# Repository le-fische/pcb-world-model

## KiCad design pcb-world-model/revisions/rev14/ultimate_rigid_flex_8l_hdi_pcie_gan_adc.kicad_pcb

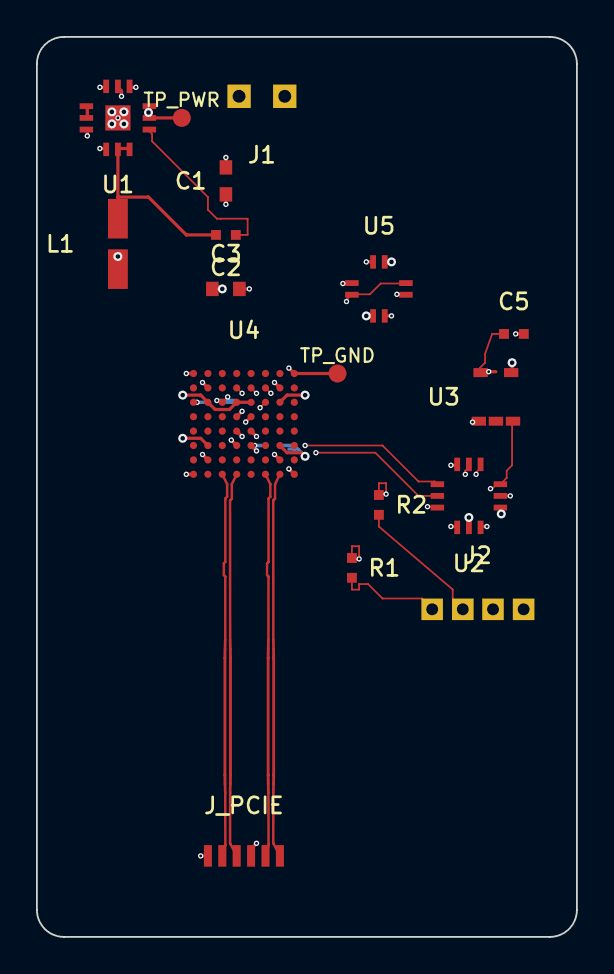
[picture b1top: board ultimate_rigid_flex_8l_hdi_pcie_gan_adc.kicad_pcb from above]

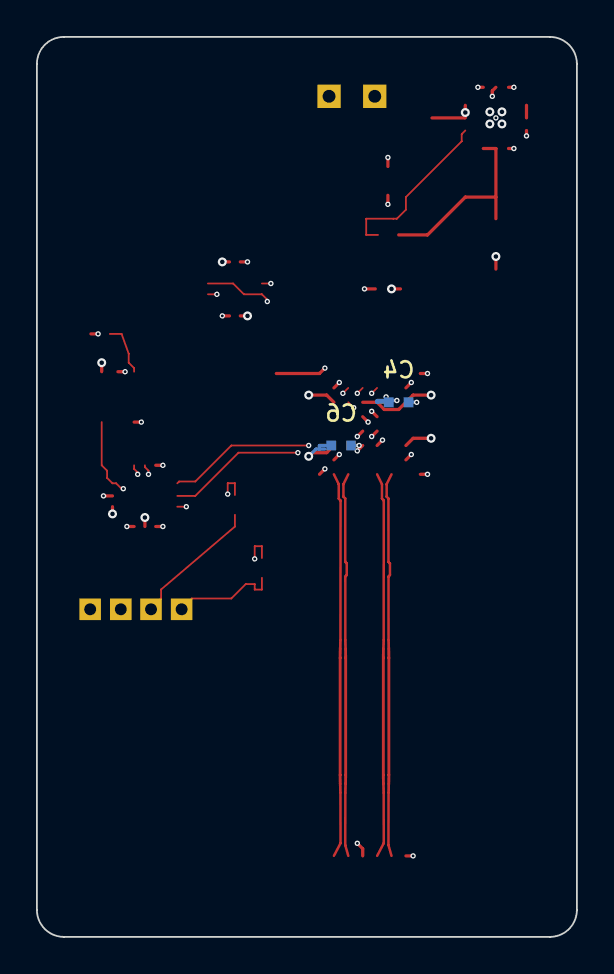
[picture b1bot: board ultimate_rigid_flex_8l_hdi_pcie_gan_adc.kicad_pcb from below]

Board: 8 copper layers, 30.0 x 50.0 mm, 19 parts (2 on the bottom side), 19 nets.

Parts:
C1: 10uF_VIN; C_0603_1608Metric
C2: 100nF_BOOT; C_0402_1005Metric
C3: 22uF_3V3; C_0603_1608Metric
C4: 100nF_PDN1; C_0402_1005Metric
C5: 100nF_VREF; C_0402_1005Metric
C6: 100nF_PDN2; C_0402_1005Metric
J1: PWR_12V_IN; PinHeader_1x02_P2.54mm_Horizontal
J2: SUBMV_ANALOG_IN; PinHeader_1x04_P1.70mm_Horizontal
J_PCIE: PCIE_GEN4_B2B; DF40C-6DP-0.8V
L1: 2.2uH_GAN_SW; L_3.5x3.5_H1.8
R1: 100R_AINP; R_0402_1005Metric
R2: 100R_AINN; R_0402_1005Metric
TP_GND: TestPoint_Pad_D1.0mm
TP_PWR: TestPoint_Pad_D1.0mm
U1: LMG5200_GAN_5A_2MHZ; QFN-12_3.5x3.5mm_P0.65mm
U2: ADS1256_24B_ADC; QFN-12_3.5x3.5mm_P0.65mm
U3: REF5025_VREF; SOT-23-5
U4: ECP5_FPGA_BGA64; BGA-64_7.2x7.2mm_Layout8x8_P0.8mm
U5: W25Q16_QSPI; QFN-8_3.0x3.0mm_P0.65mm

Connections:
ADC_AINN: R2.2, U2.5
ADC_AINP: R1.2, U2.4
ADC_CS_N: U2.9, U4.B6
BOOT_SW: C2.1, U1.7
GND: C1.2, C3.2, C4.2, C5.2, C6.2, J1.2, J2.4, J_PCIE.1, J_PCIE.4, TP_GND.1, U1.3, U1.4, U1.10, U1.12, U1.13, U2.2, U2.6, U2.10, U2.12, U3.2, U3.4, U4.A1, U4.A8, U4.B2, U4.B7, U4.D4, U4.D5, U4.E4, U4.E5, U4.F4, U4.F5, U4.G2, U4.G7, U4.H1, U4.H8, U5.4, U5.8
PCIE_CLK_N: J_PCIE.6, U4.H7
PCIE_CLK_P: J_PCIE.5, U4.H6
PCIE_TX0_N: J_PCIE.3, U4.H4
PCIE_TX0_P: J_PCIE.2, U4.H3
QSPI_CS: U4.C6, U5.2, U5.6
QSPI_SCK: U4.C3, U5.1, U5.5
SENS_N_IN: J2.2, R2.1
SENS_P_IN: J2.1, R1.1
SPI_MISO: U2.8, U4.B5
SPI_SCK: U2.7, U4.B4
SW_NODE: C2.2, L1.1, U1.5, U1.6
VCC_3V3: C3.1, C4.1, C6.1, L1.2, TP_PWR.1, U1.8, U1.9, U2.1, U2.11, U3.1, U4.C2, U4.C4, U4.C5, U4.C7, U4.F2, U4.F7, U5.3, U5.7
VIN_12V: C1.1, J1.1, U1.1, U1.2, U1.11
VREF_2V5: C5.1, J2.3, U2.3, U3.3, U3.5

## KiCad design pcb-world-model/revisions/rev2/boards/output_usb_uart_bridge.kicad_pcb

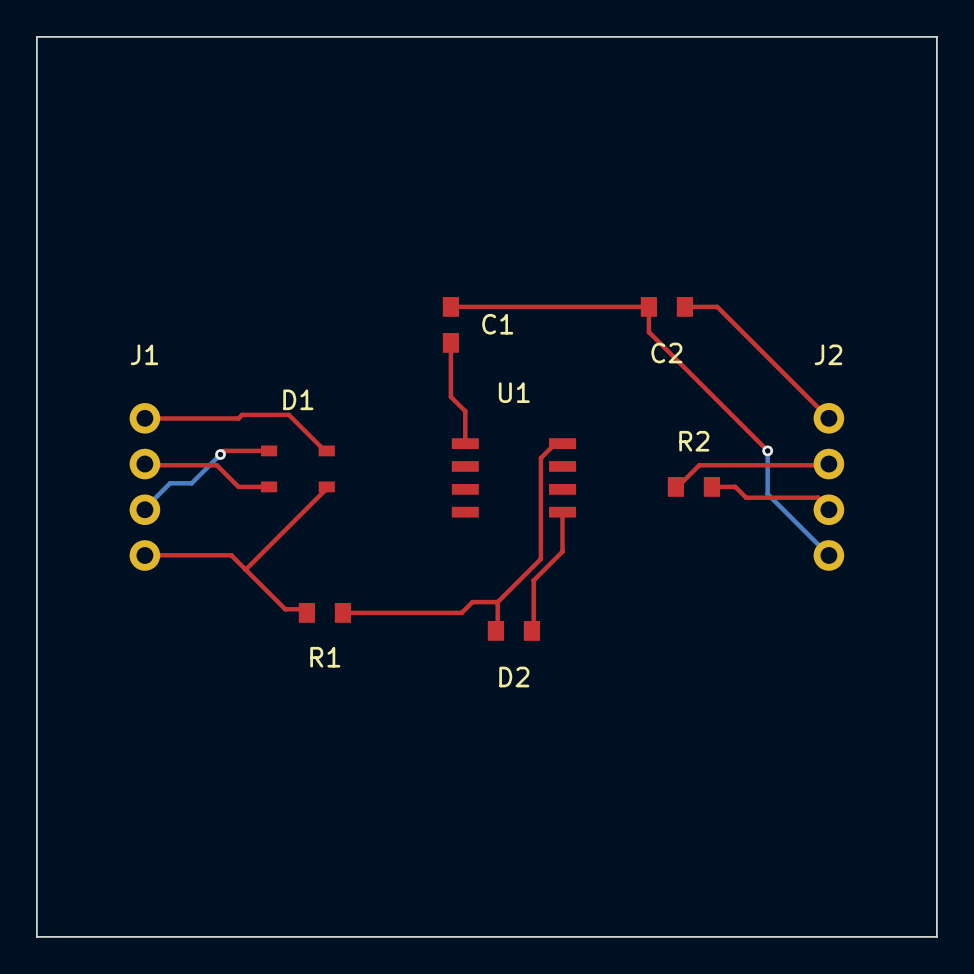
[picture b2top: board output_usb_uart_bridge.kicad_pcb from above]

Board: 2 copper layers, 50.0 x 50.0 mm, 9 parts (0 on the bottom side), 8 nets.

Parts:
C1: 10uF; C_0805_2012Metric
C2: 100nF; C_0805_2012Metric
D1: USBLC6-2SC6; SOT-23-6
D2: TX_LED; LED_0805_2012Metric
J1: USB_PORT; USB_Micro-B_Molex
J2: UART_HDR; PinHeader_1x04_P2.54mm_Vertical
R1: 470R; R_0603_1608Metric
R2: 0R_LOOP_OPT; R_0603_1608Metric
U1: CH340N_BRIDGE; SOIC-8_3.9x4.9mm_P1.27mm

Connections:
GND: C1.2, C2.2, D1.3, J1.4, J2.4, R1.2, U1.4
LED_ACT: D2.2, R1.1, U1.8
UART_RX: J2.3, R2.2, U1.7
UART_TX: J2.2, R2.1, U1.6
USB_DM: D1.2, J1.2, U1.3
USB_DP: D1.1, J1.3, U1.2
VBUS_5V: C1.1, D1.4, J1.1, U1.1
VCC_3V3: C2.1, D2.1, J2.1, U1.5

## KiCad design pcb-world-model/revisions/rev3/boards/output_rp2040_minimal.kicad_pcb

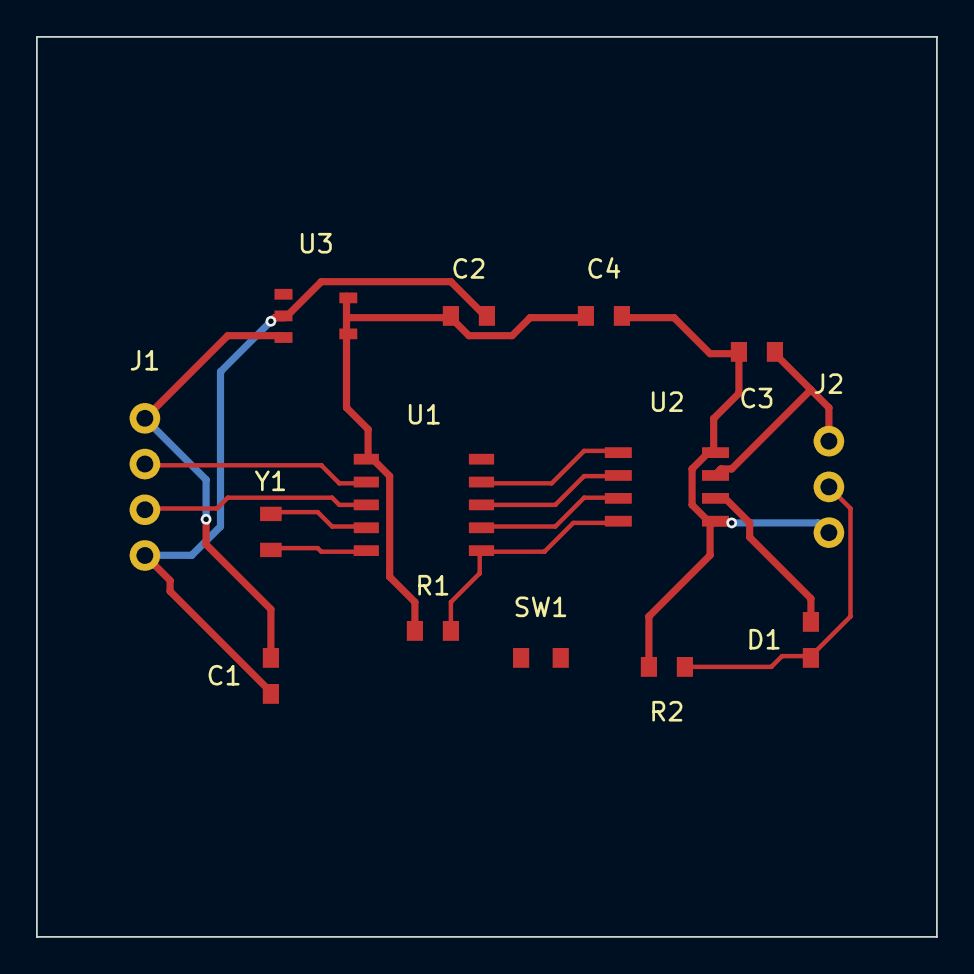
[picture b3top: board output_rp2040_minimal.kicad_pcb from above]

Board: 2 copper layers, 50.0 x 50.0 mm, 14 parts (0 on the bottom side), 12 nets.

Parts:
C1: 10uF_VBUS; C_0805_2012Metric
C2: 100nF_VDD; C_0805_2012Metric
C3: 100nF_CORE; C_0805_2012Metric
C4: 100nF_FLASH; C_0805_2012Metric
D1: PWR_LED; LED_0805_2012Metric
J1: USB_C; USB_C_Receptacle_GCT_USB4085
J2: GPIO_HDR; PinHeader_1x03_P2.54mm_Vertical
R1: 10k_CS; R_0603_1608Metric
R2: 1k_LED; R_0603_1608Metric
SW1: BOOTSEL; SW_SPST_TL3342
U1: RP2040; QFN-10_RP2040_Core
U2: W25Q16JV; SOIC-8_3.9x4.9mm_P1.27mm
U3: NCP1117-3.3; SOT-23-5
Y1: 12MHz; Crystal_SMD_3225

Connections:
GND: C1.2, C2.2, C3.2, C4.2, J1.4, J2.3, R2.2, SW1.2, U2.5, U2.8, U3.2
LED_STAT: D1.2, J2.2, R2.1, U1.6
QSPI_CLK: U1.9, U2.3
QSPI_CS: R1.2, SW1.1, U1.10, U2.4
QSPI_D0: U1.8, U2.2
QSPI_D1: U1.7, U2.1
USB_DM: J1.2, U1.2
USB_DP: J1.3, U1.3
VBUS_5V: C1.1, J1.1, U3.1, U3.3
VCC_3V3: C2.1, C3.1, C4.1, D1.1, J2.1, R1.1, U1.1, U2.6, U2.7, U3.4, U3.5
XIN: U1.4, Y1.1
XOUT: U1.5, Y1.2

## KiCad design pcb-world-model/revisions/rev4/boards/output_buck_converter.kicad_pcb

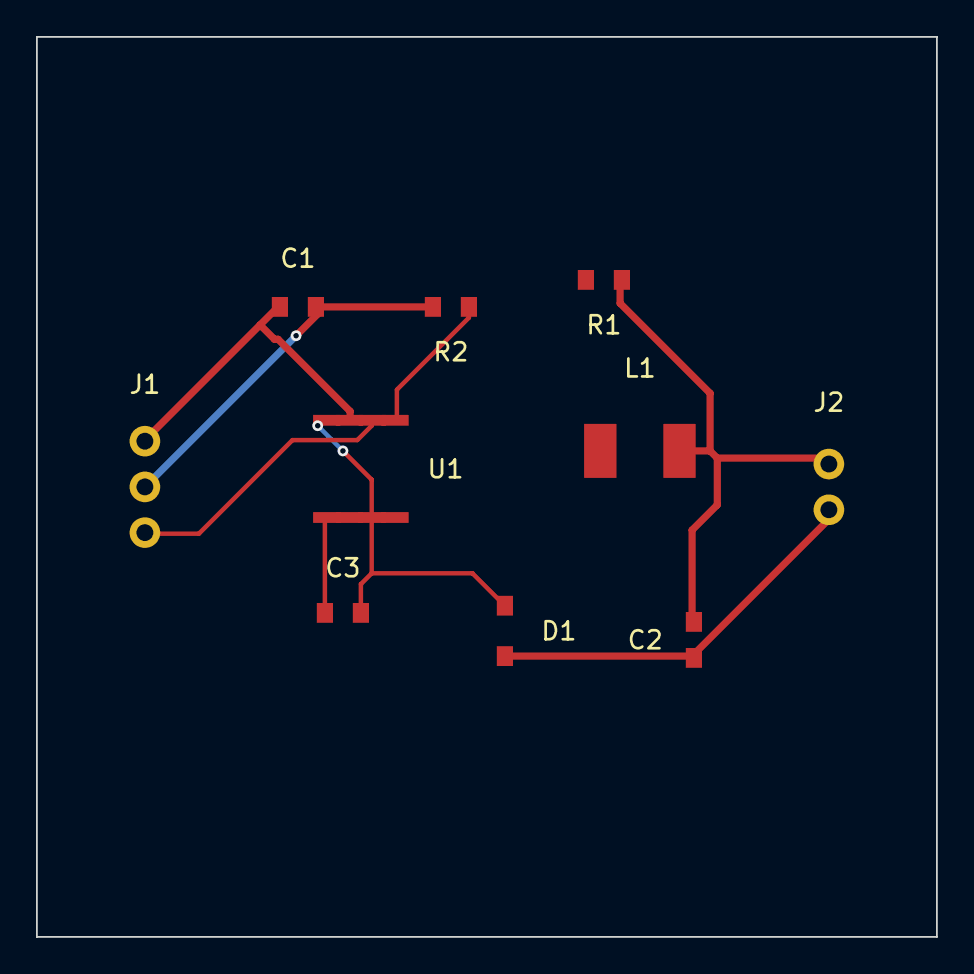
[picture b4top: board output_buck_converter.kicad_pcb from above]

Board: 2 copper layers, 50.0 x 50.0 mm, 10 parts (0 on the bottom side), 7 nets.

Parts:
C1: 22uF_IN; C_1206_3216Metric
C2: 47uF_OUT; C_1206_3216Metric
C3: 100nF_BST; C_0603_1608Metric
D1: SS34; D_SMA
J1: VIN_12V; TerminalBlock_bornier-3_P5.08mm
J2: VOUT_5V; TerminalBlock_bornier-2_P5.08mm
L1: 10uH; L_6.3x6.3_H3
R1: 100k; R_0603_1608Metric
R2: 18.7k; R_0603_1608Metric
U1: TPS54302; SOIC-8_3.9x4.9mm_P1.27mm

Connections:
BOOT: C3.1, U1.1
EN_CTRL: J1.3, U1.6
FB_DIV: R1.2, R2.1, U1.5
GND: C1.2, C2.2, D1.1, J1.2, J2.2, R2.2, U1.4
SW_NODE: C3.2, D1.2, L1.1, U1.3, U1.8
VIN_12V: C1.1, J1.1, U1.2, U1.7
VOUT_5V: C2.1, J2.1, L1.2, R1.1

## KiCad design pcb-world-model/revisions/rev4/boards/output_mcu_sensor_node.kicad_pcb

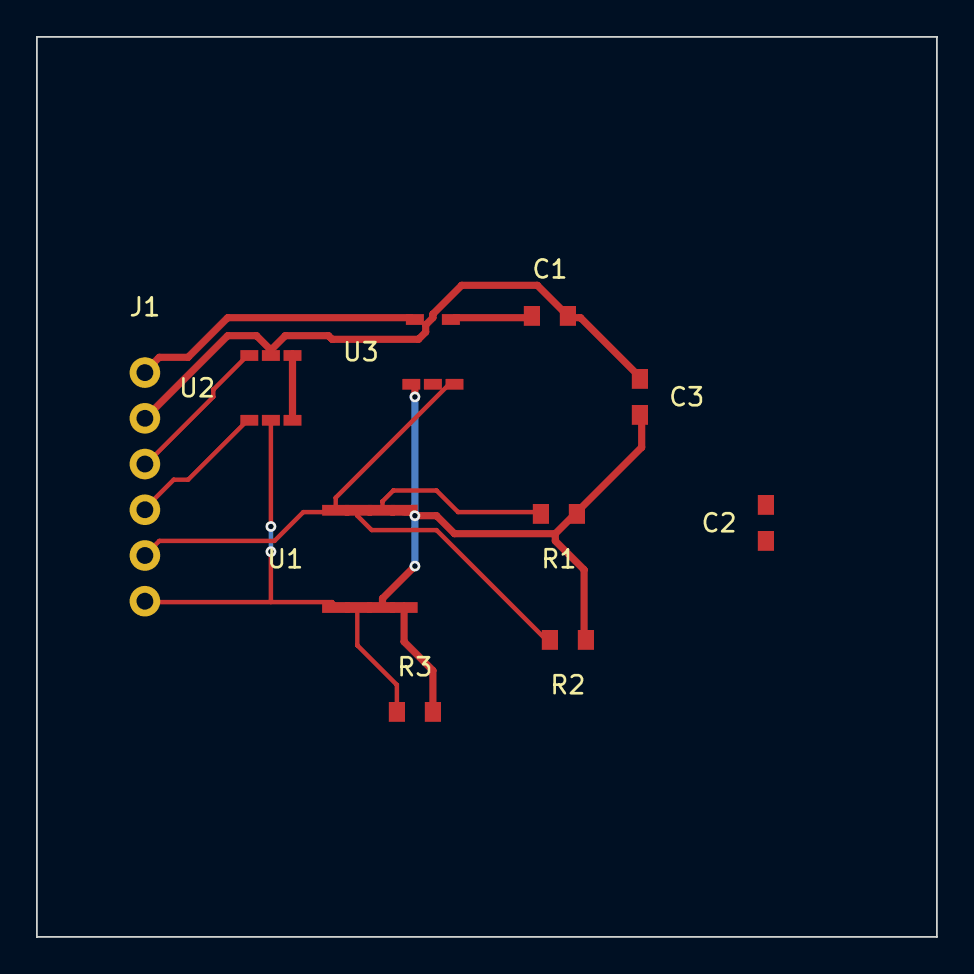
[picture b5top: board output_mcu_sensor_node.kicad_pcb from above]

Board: 2 copper layers, 50.0 x 50.0 mm, 10 parts (0 on the bottom side), 8 nets.

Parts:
C1: 10uF; C_0805_2012Metric
C2, C3: 100nF; C_0805_2012Metric
J1: I2C_HOST_HDR; PinHeader_1x06_P2.54mm_Vertical
R1, R2: 4.7k; R_0603_1608Metric
R3: 1k_LED; R_0603_1608Metric
U1: ATtiny1614; SOIC-8_3.9x4.9mm_P1.27mm
U2: BME280_I2C; SOT-23-6
U3: AP2112K-3.3; SOT-23-5

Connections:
GND: C1.2, C2.2, C3.2, J1.2, R3.2, U1.8, U2.2, U3.2
I2C_SCL: J1.4, R2.2, U1.3, U2.4
I2C_SDA: J1.3, R1.2, U1.2, U2.3
MCU_RST: J1.5, U1.4, U3.5
SENSOR_INT: J1.6, U1.5, U2.5
STATUS_LED: R3.1, U1.6
VCC_3V3: C2.1, C3.1, R1.1, R2.1, U1.1, U1.7, U2.1, U2.6, U3.4
VIN_5V: C1.1, J1.1, U3.1, U3.3

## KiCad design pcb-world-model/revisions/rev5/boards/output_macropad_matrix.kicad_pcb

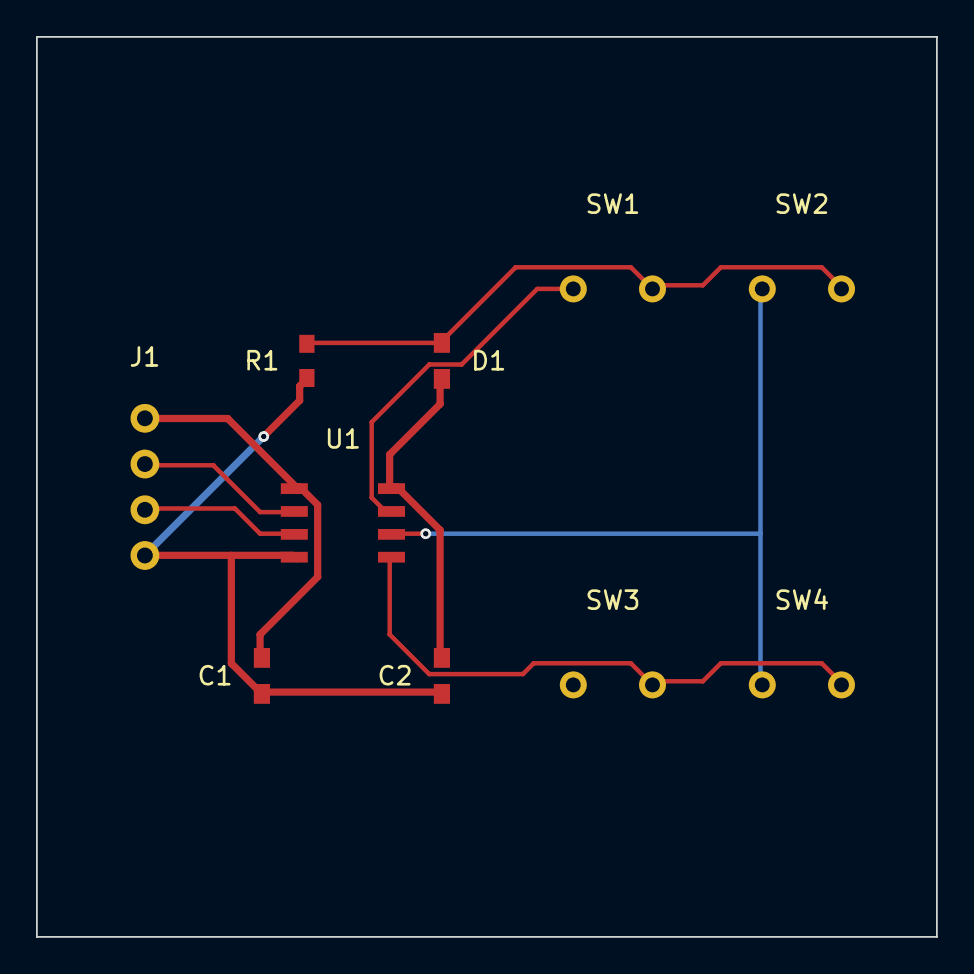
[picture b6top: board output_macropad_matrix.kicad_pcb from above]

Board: 2 copper layers, 50.0 x 50.0 mm, 10 parts (0 on the bottom side), 9 nets.

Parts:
C1: 10uF_VBUS; C_0805_2012Metric
C2: 100nF_VDD; C_0805_2012Metric
D1: ROW0_SCAN; LED_0805_2012Metric
J1: USB_HID_HDR; PinHeader_1x04_P2.54mm_Vertical
R1: 10k_ROW0; R_0603_1608Metric
SW1: KEY_1; SW_Cherry_MX_1.00u_PCB
SW2: KEY_2; SW_Cherry_MX_1.00u_PCB
SW3: KEY_3; SW_Cherry_MX_1.00u_PCB
SW4: KEY_4; SW_Cherry_MX_1.00u_PCB
U1: CH552G_HID; SOIC-8_3.9x4.9mm_P1.27mm

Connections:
COL0: SW1.1, SW3.1, U1.7
COL1: SW2.1, SW4.1, U1.6
GND: C1.2, C2.2, J1.4, R1.2, U1.4
ROW0: D1.2, R1.1, SW1.2, SW2.2
ROW1: SW3.2, SW4.2, U1.5
USB_DM: J1.2, U1.2
USB_DP: J1.3, U1.3
VBUS_5V: C1.1, J1.1, U1.1
VCC_3V3: C2.1, D1.1, U1.8
